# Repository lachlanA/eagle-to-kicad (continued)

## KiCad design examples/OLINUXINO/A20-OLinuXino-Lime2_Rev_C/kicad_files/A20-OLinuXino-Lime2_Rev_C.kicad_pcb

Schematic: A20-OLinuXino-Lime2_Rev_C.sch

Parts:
1.2V_CPU224, 1.2V_INT224, 1.5V224, 2.5V224, 3.0VA224, 3.3V224, 5VEXT224: TESTPADTESTPAD_40-ROUND; GOGO_TESTPAD_40-ROUND
5V_E224: Open; JUMPER_SJ_1_SMALLER
5V_E_SATA224: JUMPER_SJ_1_SMALLER
5V_SATA_PWR224: CON2DW02R; PENKO_DW02R
+5V224: TESTPADTESTPAD_40-ROUND; GOGO_TESTPAD_40-ROUND
BAT224: TESTPADTESTPAD_40-ROUND; GOGO_TESTPAD_40-ROUND
C1, C2, C3, C4, C5, C6, C7, C8, C9, C10, C11, C12, C13, C14, C16, C17, C18, C19, C20, C21, C22, C23, C24, C25, C26, C27, C28, C29, C30, C31, C32, C33, C34, C35, C36, C37, C38, C39, C40, C41, C42, C43, C44, C45, C46, C47, C48, C49, C50, C51, C52, C53, C54, C55, C56, C57, C58, C59, C60, C61, C62, C63, C64, C65, C66, C67, C68, C69, C70, C74, C75, C76, C92, C93, C94, C95, C96, C97, C98, C99, C100, C106, C107, C121, C126, C129, C130, C131, C132, C133, C144, C148, C164, C178, C184, C189, C194, C196: 220nF; RCL_C0402_TI
C15, C71, C77, C83, C86, C87, C118, C120, C122, C123, C124, C138, C143, C145, C147, C151, C165, C168, C177, C181, C190, C191, C192, C195, C198, C202, C203, C204, C205, C206, C207, C208, C210, C212, C213: 22uF/6.3V; RCL_C0603_DWS
C72, C73, C78, C79, C82, C84, C85, C88, C89, C90, C91, C101, C102, C103, C109, C112, C113, C114, C119, C135, C136, C137, C149, C152, C193: 100nF; RCL_C0402_TI
C80, C81: NA; RCL_C0402_TI
C104, C105: 27pF; RCL_C0603_DWS
C108, C125, C159, C171, C176, C180: 1uF; RCL_C0603_DWS
C110, C115: 10pF; RCL_C0402_TI
C111: 100n; RCL_C0402_TI
C116, C117: 33pF; RCL_C0603_DWS
C127, C128, C134, C146, C150, C155, C158, C160, C161, C162, C163, C166, C170, C172, C174, C179, C182, C183, C185, C186, C188: 10uF/6.3V; RCL_C0603_DWS
C139, C140, C141, C142, C167, C173, C187, C209: 1nF; RCL_C0402_TI
C153, C154, C156, C157: 10nF; RCL_C0402_TI
C169, C220, C221, C222, C223: NA(22uF/6.3V); RCL_C0603_DWS
C175: 22uF/6.3V/0603; RCL_C0603_DWS
C197, C199: 470nF; RCL_C0603_DWS
C200: 470uF/10V/105C; RCL_E2_5-6_3
C201, C211: 22pF; RCL_C0603_DWS
C214: 1nF/2kV/X7R/1206; RCL_C1206_5MILS_WS_ISO
C215, C216, C217, C218, C219: NA(47uF/6.3V/tant); RCL_CT3528_MIL
CHGLED224: LED/YELLOW/0603; DOUBLE-SIDE_LED-0603
D1, D2: 1N5819(S4SOD-123); GOGO_SOD-123
D3: SMBJ6.0A; OLIMEX_DISCRET_DO214AA
D4: NA(1N5822/SS34/SMA); GOGO_MLL-41
D5: 1N5822/SS34/SMA; SEMICON-SMD-IPC_MELF-MLL41
FET1, FET3, FET4: IRLML6402; PENKO_SOT23
FET2: BSS138; PENKO_SOT23
FUSE1: FSMD035; GOGO_1206
GND224: TESTPADTESTPAD_40-ROUND; GOGO_TESTPAD_40-ROUND
GND_PIN224: TESTPAD3; GOGO_TEST_PAD40_70_SQUARE
GPIO-1, GPIO-2, GPIO-3: GPH127SMT-02X20(PA-V16X-2X20-LF); CON-HARTING-ML_GPH127SMT-02X20(PA-V16X-2X20-LF)
GPIO-4: GPH127SMT-02X10(PA-V16X-2X10-LF); CON-HARTING-ML_GPH127SMT-02X10(PA-V16X-2X10-LF)
HDMI224: HDMI-SWM-19; OLIMEX_CONNECTORS_HDMI-SWM-19
IPSOUT224: TESTPADTESTPAD_40-ROUND; GOGO_TESTPAD_40-ROUND
L1, L2, L3: 0R/0805; RCL_L0805_5MIL_DWS
L4: 4.7uH/1.15A/DCR<0.1R/CD43; OLIMEX_DISCRET_CD42(43)
L5: CL470nH/0805/0.3R/250mA; RCL_L0805_5MIL_DWS
L6, L7, L8, L9, L10: FB0805/600R/2A; RCL_L0805_5MIL_DWS
L11, L12, L13, L14, L15, L16: 2.2uH/1.5A/DCR<0.1R/CD32; OLIMEX_DISCRET_CD32
LAN224: TM211Q01FM22_SH; OLIMEX_CONNECTORS_TM211Q01FM22_SH
LCD_CON224: GPH127SMT-02X20(PA-V16X-2X20-LF); CON-HARTING-ML_GPH127SMT-02X20(PA-V16X-2X20-LF)
LED1: LED/GREEN/0603; DOUBLE-SIDE_LED-0603
LIPO_BAT224: CON2DW02R; PENKO_DW02R
NAND_E224: Close; JUMPER_SJ_1_SMALLER_CLOSE_10MILS
PC3/PB8: JUMPER_SJ_2_SMALL_23_TIED
PWR224: SIDE_WTCM-TR(3X4); GOGO_SW_TAKT3X4
PWR_JACK224: YDJ-1136; GOGO_PWR_JACK_UNI_MILLING
PWR_LED224: LED/RED/0603; DOUBLE-SIDE_LED-0603
Q1: E4SB25.000F20E15(25MHz/20pF/20ppm/5x3.2mm); CRYSTAL_HCX-4S
Q3: 4SB24.000F20E15/5x3.2mm/20ppm/20pF; CRYSTAL_HCX-4S
Q4: 32768Hz/6pF; CRYSTAL_MC-306
R1, R2, R4, R5, R6, R45, R46: 2k/1%; RCL_R0402_TI
R3, R19, R28, R33, R34, R38: NA; RCL_R0402_TI
R7, R8, R14: 330R/1%; RCL_R0603_5MIL_DWS
R9, R10, R16, R17: 22R; RCL_R0402_TI
R11, R13: 0R_board_mounted; RCL_R0402_TI_0R
R12: NA(4.7k); RCL_R0402_TI
R15, R18, R22, R23, R29, R42, R44, R52, R54, R58, R62, R64, R68, R71, R78: 10k; RCL_R0402_TI
R20, R24, R36: 1k; RCL_R0402_TI
R21, R32, R37: 4.7k; RCL_R0402_TI
R25: NA(22R); RCL_R0402_TI
R26: 2.49k/1%; RCL_R0603_5MIL_DWS
R27, R30, R47, R55, R76: 47k; RCL_R0402_TI
R31: 470k; RCL_R0402_TI
R35: 10M; RCL_R0402_TI
R39, R40, R93, R94, R95, R96: NA(2.2k); RCL_R0402_TI
R41, R67, R87: 100k/1%; RCL_R0603_5MIL_DWS
R43, R69, R74: 200k/1%; RCL_R0603_5MIL_DWS
R48: NA(0R); RCL_R0603_5MIL_DWS
R49, R50: NA; RCL_R0603_5MIL_DWS
R51, R86, R91: 4.99k/1%; RCL_R0603_5MIL_DWS
R53, R63: 13k/1%; RCL_R0603_5MIL_DWS
R56, R57, R60, R61, R70, R75, R77, R79, R80, R81, R82, R88: 2.2k; RCL_R0402_TI
R59, R73: 6.8k/1%; RCL_R0603_5MIL_DWS
R65: 100R; RCL_R0603_5MIL_DWS
R66: 0.03R/1%; RCL_R1206_5MIL_WS
R72: 191R/1%; RCL_R0603_5MIL_DWS
R83: 0R(Board_Mounted); OLIMEX_DISCRET_0603_0R
R84: 1M; RCL_R0402_TI
R85: 8.25k/1%; RCL_R0603_5MIL_DWS
R89, R92: 1.1k/1%; RCL_R0603_5MIL_DWS
R90: 3.32k/1%; RCL_R0603_5MIL_DWS
RECOVERY224: SIDE_WTCM-TR(3X4); GOGO_SW_TAKT3X4
RESET224: SIDE_WTCM-TR(3X4); GOGO_SW_TAKT3X4
RM1, RM4: RA0805_(4X0402)_4B8_4.7k; OLIMEX_DISCRET_R_MATRIX_4_0402_25X625
RM2: RA0805_(4X0402)_4B8_22R; OLIMEX_DISCRET_R_MATRIX_4_0402_25X625
RM3: RA1206_(4X0603)_4B8_100K; OLIMEX_DISCRET_R_MATRIX_4
SATA224: SATA-PWA-07; OLIMEX_CONNECTORS_SATA-PWA-07
SD/MMC224: MICRO_SD/MMC_CP_NEWTFC-WPAPR-08; OLIMEX_CONNECTORS_TFC-WPAPR-08
T1: BC846B; SEMICON-SMD-IPC_SOT23
U1: A20; OLIMEX_IC_TFBGA441
U2, U3: K4B4G1646D-BCK0; OLIMEX_IC_FBGA96_SK
U4: H27UBG8T2BTR; OLIMEX_IC_TSOP48
U5: RTL8211CL-GR; OLIMEX_IC_LQFP48
U6: AT24C16BN-SH; GOGO_SO-08MN
U7, U8, U9: NA(RCLAMP0524P); OLIMEX_IC_SLP2510P8
U10, U11, U12: SY6280; OLIMEX_IC_SOT23-5
U13: AXP209(QFN48); OLIMEX_IC_QFN48
U14: MCP120T475I-TT; GOGO_SOT23
U15, U17: SY8008C(AA)C; OLIMEX_IC_SOT23-5
U16: SY7208(SOT23-6); OLIMEX_IC_SOT23-6
U18, U19, U20, U21: FIDUCIAL; SPARKFUNEAGLE-6-6-07_FIDUCIAL-1X3
UART0: HN1X3; PENKO_HN1X3
USB_HOST1, USB_HOST2: USB_A_VERTICAL; OLIMEX_CONNECTORS_USB_A_VERTICAL_PTH
USB_OTG224: USB-OTG; OLIMEX_CONNECTORS_USB_MINI_9PIN
VR1: AP1231-2.5V(SOT23-5); OLIMEX_DISCRET_SOT-23-5

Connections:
+5V: GPIO-1.1, GPIO-2.1, GPIO-3.1, LCD_CON224.1
/5VEXT: 5VEXT224.1, 5V_E224.1, C158.2, C200.+, D3.C, D4.A, FET3.3 (D), PWR_JACK224.+, R78.1, R82.1, U13.32 (ACIN), U13.33 (ACIN), U14.2 (VCC)
/+5V: 5V_E224.2, 5V_E_SATA224.1, +5V224.1, C137.1, C146.1, C150.1, D4.K (C), FET1.2 (S), FET3.2 (S), FET4.2 (S), FUSE1.1, R45.2, R46.2, R68.1, R76.2, U10.5 (IN), U11.5 (IN), U12.5 (IN)
/+5V_OTG_PWR: C136.1, C163.2, L6.1, R67.1, U13.31 (VBUS), USB_OTG224.VBUS
/+24V: BAT224.1, C159.2, C161.1, C207.2, LIPO_BAT224.1, R66.2, U13.38 (BAT), U13.39 (BAT), U13.42 (BATSENSE)
/AVDD1: C71.2, C72.2, C73.2, L1.2, U5.6 (AVDD33), U5.41 (AVDD33)
/AVDD/DVDD(1.05V): C86.2, C87.2, C88.2, C89.2, C90.2, C91.2, C101.2, U5.3 (FB10), U5.10 (AVDD10), U5.28 (DVDD10), U5.36 (DVDD10), U5.40 (AVDD10)
/BA0: U1.K3 (SBA0), U2.M2 (BA0), U3.M2 (BA0)
/BA1: U1.L4 (SBA1), U2.N8 (BA1), U3.N8 (BA1)
/BA2: U1.K4 (SBA2), U2.M3 (BA2), U3.M3 (BA2)
/CASN: U1.U3 (SCAS), U2.K3 (#CAS), U3.K3 (#CAS)
/CKE: U1.N3 (SCKE0), U2.K9 (CKE), U3.K9 (CKE)
/CLK: R9.1, U2.J7 (CK), U3.J7 (CK)
/CLK125: R25.1, U1.D13 (ECOL/CAN_TX/UART1_DCD/PA16)
/CLKN: R10.1, U2.K7 (#CK), U3.K7 (#CK)
/CPU-REF: C2.2, C13.2, C80.2, R2.1, R3.2, R5.2, U1.AA8 (SVREF3), U1.H3 (SVREF0), U1.H4 (SVREF1), U1.Y5 (SVREF2)
/DDR3_ODT: R13.1, U2.K1 (ODT), U3.K1 (ODT)
/DDR3_RST: R6.1, R11.1, U2.T2 (#RESET), U3.T2 (#RESET)
/DDR_VREF: C1.2, C14.2, R1.1, R3.1, R4.2, U2.H1 (VREFDQ), U2.M8 (VREFCA), U3.H1 (VREFDQ), U3.M8 (VREFCA)
/DQ0: U1.AB4 (SDQ0), U2.E3 (DQL0)
/DQ1: U1.AC7 (SDQ1), U2.F7 (DQL1)
/DQ2: U1.AC4 (SDQ2), U2.F2 (DQL2)
/DQ3: U1.AB8 (SDQ3), U2.F8 (DQL3)
/DQ4: U1.AC8 (SDQ4), U2.H3 (DQL4)
/DQ5: U1.AB5 (SDQ5), U2.H8 (DQL5)
/DQ6: U1.AB7 (SDQ6), U2.G2 (DQL6)
/DQ7: U1.AC3 (SDQ7), U2.H7 (DQL7)
/DQ8: U1.AB2 (SDQ8), U2.D7 (DQU0)
/DQ9: U1.Y1 (SDQ9), U2.C3 (DQU1)
/DQ10: U1.AC2 (SDQ10), U2.C8 (DQU2)
/DQ11: U1.Y2 (SDQ11), U2.C2 (DQU3)
/DQ12: U1.AA1 (SDQ12), U2.A7 (DQU4)
/DQ13: U1.AB3 (SDQ13), U2.A2 (DQU5)
/DQ14: U1.W2 (SDQ14), U2.B8 (DQU6)
/DQ15: U1.AC1 (SDQ15), U2.A3 (DQU7)
/DQ16: U1.N1 (SDQ16), U3.E3 (DQL0)
/DQ17: U1.T2 (SDQ17), U3.F7 (DQL1)
/DQ18: U1.N2 (SDQ18), U3.F2 (DQL2)
/DQ19: U1.U1 (SDQ19), U3.F8 (DQL3)
/DQ20: U1.U2 (SDQ20), U3.H3 (DQL4)
/DQ21: U1.P1 (SDQ21), U3.H8 (DQL5)
/DQ22: U1.T1 (SDQ22), U3.G2 (DQL6)
/DQ23: U1.M2 (SDQ23), U3.H7 (DQL7)
/DQ24: U1.L1 (SDQ24), U3.D7 (DQU0)
/DQ25: U1.H1 (SDQ25), U3.C3 (DQU1)
/DQ26: U1.L2 (SDQ26), U3.C8 (DQU2)
/DQ27: U1.H2 (SDQ27), U3.C2 (DQU3)
/DQ28: U1.J1 (SDQ28), U3.A7 (DQU4)
/DQ29: U1.M1 (SDQ29), U3.A2 (DQU5)
/DQ30: U1.G2 (SDQ30), U3.B8 (DQU6)
/DQ31: U1.K2 (SDQ31), U3.A3 (DQU7)
/DVDD33: C77.2, C78.2, C79.2, C82.2, L2.2, R18.1, R31.1, U5.15 (DVDD33), U5.21 (DVDD33), U5.37 (DVDD33)
/EPHY-RST#: R38.1, U1.C13 (ETXERR/CAN_RX/UART1_RING/PA17)
/EXTEN: U13.20 (EXTEN), U16.4 (EN), U17.1 (EN)
/FMINL: U1.Y20 (FMINL)
/FMINR: U1.Y21 (FMINR)
/GMDC: U1.E10 (EMDC/UART1_RX/PA11), U5.30 (MDC)
/GMDIO: R24.1, U1.D11 (EMDIO/UART6_TX/UART1_RTS/PA12), U5.31 (MDIO)
/GPIO1: R67.2, R69.1, U13.18 (GPIO1)
/GRXCK: R17.2, U1.D9 (ERXCK/SPI3_MISO/PA8)
/GRXD0: RM2.4.2 (2), U1.E6 (ERXD0/SPI1_MISO/PA3)
/GRXD1: RM2.3.2 (2), U1.D6 (ERXD1/SPI1_MOSI/PA2)
/GRXD2: RM2.2.2 (2), U1.E5 (ERXD2/SPI1_CLK/PA1)
/GRXD3: RM2.1.2 (2), U1.D5 (ERXD3/SPI1_CS0/PA0)
/GTXCK: U1.E12 (ECRS/UART7_RX/UART1_DSR/PA15), U5.22 (TXC)
/GTXCTL: U1.E11 (ETXEN/UART6_RX/UART1_CTS/PA13), U5.27 (TXCTL/TXEN)
/GTXD0: U1.E8 (ETXD0/SPI3_MOSI/PA7), U5.23 (TXD[0])
/GTXD1: U1.D8 (ETXD1/SPI3_CLK/PA6), U5.24 (TXD[1])
/GTXD2: U1.E7 (ETXD2/SPI3_CS0/PA5), U5.25 (TXD[2])
/GTXD3: U1.D7 (ETXD3/SPI1_CS1/PA4), U5.26 (TXD[3])
/HCEC: HDMI224.13, U1.P23 (CEC_HDMI), U9.1 (IN1), U9.10 (OUT1)
/HDMI_5V_SOURCE: FUSE1.2, HDMI224.18
/HHPD: HDMI224.19, R47.1, U1.P22 (HPD_HDMI), U9.5 (IN4), U9.6 (OUT4)
/HPCOM: U1.AA19 (HPCOM), U1.AA20 (HPCOMFB)
/HPOUTL: U1.Y19 (HPOUTL)
/HPOUTR: U1.W19 (HPOUTR)
/HSCL: HDMI224.15, R45.1, U1.R23 (SCL_HDMI), U9.2 (IN2), U9.9 (OUT2)
/HSDA: HDMI224.16, R46.1, U1.R22 (SDA_HDMI), U9.4 (IN3), U9.7 (OUT3)
/HTX0N: HDMI224.9, U1.V22 (TX0N_HDMI), U8.2 (IN2), U8.9 (OUT2)
/HTX0P: HDMI224.7, U1.V23 (TX0P_HDMI), U8.1 (IN1), U8.10 (OUT1)
/HTX1N: HDMI224.6, U1.U22 (TX1N_HDMI), U7.5 (IN4), U7.6 (OUT4)
/HTX1P: HDMI224.4, U1.U23 (TX1P_HDMI), U7.4 (IN3), U7.7 (OUT3)
/HTX2N: HDMI224.3, U1.T22 (TX2N_HDMI), U7.2 (IN2), U7.9 (OUT2)
/HTX2P: HDMI224.1, U1.T23 (TX2P_HDMI), U7.1 (IN1), U7.10 (OUT1)
/HTXCN: HDMI224.12, U1.W22 (TXCN_HDMI), U8.5 (IN4), U8.6 (OUT4)
/HTXCP: HDMI224.10, U1.W23 (TXCP_HDMI), U8.4 (IN3), U8.7 (OUT3)
/IPSOUT: C155.2, C162.1, C170.1, C174.1, C182.2, C186.1, C202.1, C208.2, C210.1, IPSOUT224.1, L15.1, R70.1, U13.7 (VIN2), U13.13 (LDO24IN), U13.14 (VIN3), U13.21 (APS), U13.34 (IPSOUT), U13.35 (IPSOUT), U13.40 (LDO3IN), U13.44 (VIN1), U15.4 (IN), U16.5 (IN), U17.4 (IN)
/LAN_SH: C214.2, LAN224.SH1, LAN224.SH2
/LCD_CLK: U1.Y9 (LCD0_CLK/SMC_VCCEN/PD24)
/LCD_D0: U1.AB15 (LCD0_D0/LVDS0_VP0/PD0)
/LCD_D1: U1.AC15 (LCD0_D1/LVDS0_VN0/PD1)
/LCD_D2: U1.AB14 (LCD0_D2/LVDS0_VP1/PD2)
/LCD_D3: U1.AC14 (LCD0_D3/LVDS0_VN1/PD3)
/LCD_D4: U1.AB13 (LCD0_D4/LVDS0_VP2/PD4)
/LCD_D5: U1.AC13 (LCD0_D5/LVDS0_VN2/PD5)
/LCD_D6: U1.AB12 (LCD0_D6/LVDS0_VPC/PD6)
/LCD_D7: U1.AC12 (LCD0_D7/LVDS0_VNC/PD7)
/LCD_D8: U1.AB11 (LCD0_D8/LVDS0_VP3/PD8)
/LCD_D9: U1.AC11 (LCD0_D9/LVDS0_VN3/PD9)
/LCD_D10: U1.Y15 (LCD0_D10/LVDS1_VP0/PD10)
/LCD_D11: U1.AA15 (LCD0_D11/LVDS1_VN0/PD11)
/LCD_D12: U1.Y14 (LCD0_D12/LVDS1_VP1/PD12)
/LCD_D13: U1.AA14 (LCD0_D13/LVDS1_VN1/PD13)
/LCD_D14: U1.Y13 (LCD0_D14/LVDS1_VP2/PD14)
/LCD_D15: U1.AA13 (LCD0_D15/LVDS1_VN2/PD15)
/LCD_D16: U1.Y12 (LCD0_D16/LVDS1_VPC/PD16)
/LCD_D17: U1.AA12 (LCD0_D17/LVDS1_VNC/PD17)
/LCD_D18: U1.Y11 (LCD0_D18/LVDS1_VP3/PD18)
/LCD_D19: U1.AA11 (LCD0_D19/LVDS1_VN3/PD19)
/LCD_D20: U1.Y10 (LCD0_D20/CSI1_MCLK/PD20)
/LCD_D21: U1.AA10 (LCD0_D21/SMC_VPPEN/PD21)
/LCD_D22: U1.AB10 (LCD0_D22/SMC_VPPPP/PD22)
/LCD_D23: U1.AC10 (LCD0_D23/SMC_DET/PD23)
/LCD_DE: U1.AA9 (LCD0_DE/SMC_RST/PD25)
/LCD_HSYNC: U1.AB9 (LCD0_HSYNC/SMC_SLK/PD26)
/LCD_PWR: U1.C4 (LCD1_D8/ATAD4/KP_IN0/MS_D0/EINT8/CSI1_D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)
/LCD_VSYNC: U1.AC9 (LCD0_VSYNC/SMC_SDA/PD27)
/LDO3_2.8V: C106.2, C185.1, U1.F19 (VCC_CSI0), U13.41 (LDO3)
/LDO4_2.8V: C107.2, C188.1, U1.E18 (VCC_CSI1), U13.11 (LDO4)
/LINEINL: U1.AB20 (LINEINL)
/LINEINR: U1.AB21 (LINEINR)
/LRADC0: C209.1, R87.2, U1.AB23 (LRADC0)
/LRADC1: U1.AB22 (LRADC1)
/MDI[0]+: LAN224.1, U5.1 (MDI[0]+)
/MDI[0]-: LAN224.2, U5.2 (MDI[0]-)
/MDI[1]+: LAN224.3, U5.4 (MDI[1]+)
/MDI[1]-: LAN224.4, U5.5 (MDI[1]-)
/MDI[2]+: LAN224.7, U5.8 (MDI[2]+)
/MDI[2]-: LAN224.8, U5.9 (MDI[2]-)
/MDI[3]+: LAN224.9, U5.11 (MDI[3]+)
/MDI[3]-: LAN224.10, U5.12 (MDI[3]-)
/MIC1OUTN: U1.AC23 (MIC1OUTN)
/MIC1OUTP: U1.AC22 (MIC1OUTP)
/MICIN1: U1.AC20 (MICIN1)
/MICIN2: U1.AC21 (MICIN2)
/N$1: C133.2, C134.2, U1.AC19 (HPVCC)
/N$2: R14.2, U1.AA7 (SZQ)
/N$3: R7.2, U2.L8 (ZQ)
/N$4: CHGLED224.A, R70.2
/N$5: PC3/PB8.2, R71.2
/N$7: UART0.2
/N$8: L14.1, U15.3 (LX)
/N$9: C171.2, U13.19 (GPIO0/LDO)
/N$10: R27.2
/N$11: CHGLED224.C, U13.36 (CHGLED)
/N$12: R80.1, U13.27 (LDO1SET)
/N$13: C151.2, C217.+, C218.+, C221.2, C222.2, C223.2, L10.1, U12.1 (OUT)
/N$14: C110.2, Q4.1, R35.1, U1.F1 (CLK32K_IN)
/N$15: R8.2, U3.L8 (ZQ)
/N$16: U5.48 (REG_OUT)
/N$17: C175.1, R71.1, R73.2, T1.1 (B)
/N$18: FET1.1 (G), R68.2, T1.3 (C)
/N$19: C201.2, R86.2, R90.1, U15.5 (FB)
/N$20: R26.2, U5.46 (RSET)
/N$21: FET3.1 (G), R76.1
/N$22: C104.2, Q1.2, U5.42 (CKXTAL1)
/N$23: C205.1, C206.1, D5.1 (C), FET4.3 (D), R85.2
/N$24: 5V_E_SATA224.2, 5V_SATA_PWR224.1, C168.2, C169.2, FET1.3 (D)
/N$25: C105.2, Q1.1, U5.43 (CKXTAL2)
/N$26: C111.2, R31.2, R34.2, R38.2, U5.29 (PHYRSTB)
/N$27: C102.2, LAN224.5
/N$28: C103.2, LAN224.6
/N$29: R33.1, R37.1, U5.38 (RXDLY/LED_10/LED2)
/N$30: LAN224.12, R36.2
/N$31: LAN224.11, R32.2, U5.35 (PHY_AD1/LED_1000/LED1)
/N$33: FET4.1 (G), R78.2, R84.2, U14.1 (RESET)
/N$34: R18.2, R19.2, U5.39 (ENSWREG)
/N$35: LAN224.13, R20.2
/N$36: C81.1, R17.1, U5.19 (RXC)
/N$37: R15.1, R16.1, U5.13 (RXCTL/RXDV)
/N$38: R75.1
/N$42: C197.2, U1.AA16 (VRP_TVIN)
/N$43: RM2.4.1 (1), U5.14 (RXD[0])
/N$44: R12.1, RM1.3.1 (1), RM2.3.1 (1), U5.16 (RXD[1]/TXDLY)
/N$46: RM1.2.1 (1), RM2.2.1 (1), U5.17 (RXD[2]/AN0)
/N$48: RM1.1.1 (1), RM2.1.1 (1), U5.18 (RXD[3]/AN1)
/N$50: LAN224.14, R21.1, U5.34 (PHY_AD0/LED_DUPLEX/LED0)
/N$52: R25.2, U5.32 (CLK125)
/N$58: R44.1, SD/MMC224.10 (PACK1), SD/MMC224.11 (PACK2), SD/MMC224.12 (PACK3), SD/MMC224.13 (PACK4)
/N$64: L16.1, U17.3 (LX)
/N$66: C211.2, R91.2, R92.1, U17.5 (FB)
/N$99: R53.2, U10.3 (ISET)
/N$100: C138.2, C219.+, L6.2, R51.2, U10.1 (OUT)
/N$101: R63.2, U12.3 (ISET)
/N$106: C153.2, SATA224.2 (A+)
/N$111: C152.1, L10.2, USB_HOST2.1
/N$112: C154.2, SATA224.3 (A-)
/N$113: C156.2, SATA224.5 (B-)
/N$114: C157.2, SATA224.6 (B+)
/N$116: C115.2, Q4.4 (2), R35.2, U1.F2 (CLK32K_OUT)
/N$119: R72.2, U1.V21 (REXT_SATA)
/N$120: R74.2, U13.23 (BIAS)
/N$122: C128.2, C129.2, U1.W21 (VRP)
/N$123: D5.2 (A), L15.2, U16.1 (LX)
/N$124: C112.2, R28.2, R29.2, U4.19 (#WP)
/N$125: R65.2, U13.37 (TS)
/N$126: R85.1, R89.1, U16.3 (FB)
/N$127: L11.1, U13.45 (LX1)
/N$128: C159.1, C160.1, L11.2, R66.1, U13.43 (CHSENSE)
/N$129: PWR_LED224.A, R82.2
/N$130: L12.1, U13.8 (LX2)
/N$131: L13.1, U13.15 (LX3)
/N$132: C180.2, U13.24 (VREF)
/N$133: C125.2, U1.W20 (VRA1)
/N$137: R59.2, U11.3 (ISET)
/N$139: C187.2, R75.2, U13.47 (PWRON)
/N$140: R77.2, U13.4 (N_OE)
/N$176: C126.2, C127.2, R43.1, U1.V20 (VRA2)
/N$190: R48.1, U1.T10 (JTAG_SEL)
/N$193: L9.2, USB_HOST1.P$3 (5), USB_HOST1.P$4 (6), USB_HOST2.P$3 (5), USB_HOST2.P$4 (6)
/N$194: C149.1, L8.2, USB_HOST1.1
/N$195: C147.2, C215.+, C216.+, C220.2, L8.1, U11.1 (OUT)
/N$223: C199.2, U1.Y16 (VRN_TVIN)
/N$229: R49.1
/N$230: R50.1
/N$231: LED1.A, R88.2
/N$232: NAND_E224.1, R23.2, U4.9 (#CE)
/N$266: L7.2, USB_OTG224.GND1, USB_OTG224.GND2, USB_OTG224.GND3, USB_OTG224.GND4
/NALE: U1.M22 (NALE/SPI0_MISO/PC1), U4.17 (ALE)
/NCE0: NAND_E224.2, U1.K23 (NCE0/PC4)
/NCLE: U1.L23 (NCLE/SPI0_CLK/PC2), U4.16 (CLE)
/NDQ0: U1.H23 (NDQ0/SDC2_D0/PC8), U4.29 (I/O0)
/NDQ1: U1.H22 (NDQ1/SDC2_D1/PC9), U4.30 (I/O1)
/NDQ2: U1.G23 (NDQ2/SDC2_D2/PC10), U4.31 (I/O2)
/NDQ3: U1.G22 (NDQ3/SDC2_D3/PC11), U4.32 (I/O3)
/NDQ4: U1.H21 (NDQ4/PC12), U4.41 (I/O4)
/NDQ5: U1.H20 (NDQ5/PC13), U4.42 (I/O5)
/NDQ6: U1.G21 (NDQ6/PC14), U4.43 (I/O6)
/NDQ7: U1.G20 (NDQ7/PC15), U4.44 (I/O7)
/NMI_N: R27.1, U1.F5 (NMI#), U13.48 (IRQ/WAKEUP)
/NRB0: R22.2, U1.J23 (NRB0/SDC2_CMD/PC6), U4.7 (R/#B)
/NRE: U1.K22 (NRE#/PC5), U4.8 (#RE)
/NWE: U1.M23 (NWE#/SPI0_MOSI/PC0), U4.18 (#WE)
/ODT0: R13.2, U1.AA5 (ODT0)
/PA9: U1.E9 (ERXERR/SPI3_CS1/PA9)
/PA14: U1.D12 (ETXCK/UART7_TX/UART1_DTR/PA14)
/PB2/PWM0: U1.A14 (PWM0/PB2)
/PB3: R49.2, U1.B14 (IR0_TX/SPDIF_MCLK/STANBYWFI/PB3)
/PB4: R50.2, U1.A13 (IR0_RX/PB4)
/PB5: U1.B13 (I2S_MCLK/AC97_MCLK/PB5)
/PB6: U1.A12 (I2S_BCLK/AC97_BCLK/PB6)
/PB7: U1.B12 (I2S_LRCK/AC97_SYNC/PB7)
/PB8/SATA-PWR-EN: PC3/PB8.1, U1.A11 (I2S_DO0/AC97_DO/PB8)
/PB9: U1.C12 (I2S_DO1/PB9)
/PB10: U1.C11 (I2S_DO2/PB10)
/PB11: U1.C10 (I2S_DO3/PB11)
/PB12: U1.C9 (I2S_DI/AC97_DI/SPDIF_DI/PB12)
/PB13: U1.B11 (SPI2_CS1/SPDIF_DO/PB13)
/PB14: RM4.1.1 (1), U1.A10 (JTAG_MS0/SPI2_CS0/PB14)
/PB15: RM4.2.1 (1), U1.B10 (JTAG_CK0/SPI2_CLK/PB15)
/PB16: U1.A9 (JTAG_DO0/SPI2_MOSI/PB16)
/PB17: RM4.4.1 (1), U1.B9 (JTAG_DI0/SPI2_MISO/PB17)
/PB18: R39.2, R61.1, U1.A8 (TWI1_SCK/PB18), U6.6 (SCL)
/PB19: R40.1, R60.1, U1.B8 (TWI1_SDA/PB19), U6.5 (SDA)
/PB20: R57.1, U1.C8 (TWI2_SCK/PB20)
/PB21: R56.1, U1.C7 (TWI2_SDA/PB21)
/PC3/SATA-PWR-EN: PC3/PB8.3, U1.L22 (NCE1/PC3)
/PC7: U1.J22 (NRB1/SDC2_CLK/PC7)
/PC16/NWP: R28.1, U1.M21 (NWP/PC16)
/PC17/USB0-DRV: R52.2, U1.F23 (NCE2/PC17), U10.4 (EN), U13.6 (N_VBUSEN)
/PC18: U1.F22 (NCE3/PC18)
/PC19: U1.L21 (NCE4/SPI2_CS0/PC19)
/PC20: U1.K21 (NCE5/SPI2_CLK/PC20)
/PC21: U1.J21 (NCE6/SPI2_MOSI/PC21)
/PC22: U1.J20 (NCE7/SPI2_MISO/PC22)
/PC23: U1.G19 (SPI0_CS0/PC23)
/PC24: U1.F21 (NDQS/PC24)
/PE0: U1.E23 (TS0_CLK/CSI0_PCLK/PE0)
/PE1: U1.E22 (TS0_ERR/CSI0_MCLK/PE1)
/PE2: U1.D23 (TS0_SYNC/CSI0_HSYNC/PE2)
/PE3: U1.D22 (TS0_DVLD/CSI0_VSYNC/PE3)
/PE4: U1.C23 (TS0_D0/CSI0_D0/PE4)
/PE5: U1.C22 (TS0_D1/CSI0_D1/PE5)
/PE6: U1.B23 (TS0_D2/CSI0_D2/PE6)
/PE7: U1.B22 (TS0_D3/CSI0_D3/PE7)
/PE8: U1.A23 (TS0_D4/CSI0_D4/PE8)
/PE9: U1.A22 (TS0_D5/CSI0_D5/PE9)
/PE10: U1.B21 (TS0_D6/CSI0_D6/PE10)
/PE11: U1.A21 (TS0_D7/CSI0_D7/PE11)
/PG0: U1.F20 (TS1_CLK/CSI1_PCLK/SDC1_CMD/PG0)
/PG1: U1.E21 (TS1_ERR/CSI1_MLCK/SDC1_CLK/PG1)
/PG2: U1.E20 (TS1_SYNC/CSI1_HSYNC/SDC1_D0/PG2)
/PG3: U1.D21 (TS1_DVLD/CSI1_VSYNC/SDC1_D1/PG3)
/PG4: U1.D20 (TS1_D0/CSI1_D0/SDC1_D2/CSI0_D8/PG4)
/PG5: U1.C21 (TS1_D1/CSI1_D1/SDC1_D3/CSI0_D9/PG5)
/PG6: U1.E19 (TS1_D2/CSI1_D2/UART3_TX/CSI0_D10/PG6)
/PG7: U1.C20 (TS1_D3/CSI1_D3/UART3_RX/CSI0_D11/PG7)
/PG8: U1.D19 (TS1_D4/CSI1_D4/UART3_RTS/CSI0_D12/PG8)
/PG9: U1.C19 (TS1_D5/CSI1_D5/UART3_CTS/CSI0_D13/PG9)
/PG10: U1.D18 (TS1_D6/CSI1_D6/UART4_TX/CSI0_D14/PG10)
/PG11: U1.C18 (TS1_D7/CSI1_D7/UART4_RX/CSI0_D15/PG11)
/PH0: U1.A6 (LCD1_D0/ATAA0/UART3_TX/EINT0/CSI1_D0/PH0)
/PH2/LED: R88.1, U1.C6 (LCD1_D2/ATAA2/UART3_RTS/EINT2/CSI1_D2/P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)
/PH7: U1.B4 (LCD1_D7/ATAD3/UART5_RX/MS_CLK/EINT7/CSI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)
/PH9: U1.D4 (LCD1_D9/ATAD5/KP_IN1/MS_D1/EINT9/CSI1_D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)
/PH10: U1.A3 (LCD1_D10/ATAD6/KP_IN2/MS_D2/EINT10/CSI1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)
/PH11: U1.B3 (LCD1_D11/ATAD7/KP_IN3/MS_D3/EINT11/CSI1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)
/PH12: U1.C3 (LCD1_D12/ATAD8/PS2_SCK1/EINT12/CSI1_D12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)
/PH13: U1.A2 (LCD1_D13/ATAD9/PS2_SDA1/SMC_RST/EINT13/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)
/PH14: U1.B2 (LCD1_D14/ATAD10/KP_IN4/SMC_VPPEN/EINT14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)
/PH15: U1.A1 (LCD1_D15/ATAD11/KP_IN5/SMC_VPPPP/EINT15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)
/PH16: U1.B1 (LCD1_D16/ATAD12/KP_IN6/SMC_DET/EINT16/C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)
/PH17: U1.C1 (LCD1_D17/ATAD13/KP_IN7/SMC_VCCEN/EINT17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)
/PH18: U1.C2 (LCD1_D18/ATAD14/KP_OUT0/SMC_SLK/EINT18/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)
/PH19: U1.D1 (LCD1_D19/ATAD15/KP_OUT1/SMC_SDA/EINT19/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)
/PH20: U1.D2 (LCD1_D20/ATAOE/CAN_TX/EINT20/CSI1_D20/P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)
/PH21: U1.D3 (LCD1_D21/ATADREQ/CAN_RX/EINT21/CSI1_D21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)
/PH22: U1.E1 (LCD1_D22/ATADACK/KP_OUT2/SDC1_CMD/CSI1_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)
/PH23: U1.E2 (LCD1_D23/ATACS0/KP_OUT3/SDC1_CLK/CSI1_D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)
/PH24: U1.E3 (LCD1_CLK/ATACS1/KP_OUT4/SDC1_D0/CSI1_PC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)
/PH25: U1.E4 (LCD1_DE/ATAIORDY/KP_OUT5/SDC1_D1/CSI1_F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)
/PH26: U1.F3 (LCD1_HSYNC/ATAIOR/KP_OUT6/SDC1_D2/CSI1_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)
/PH27: U1.F4 (LCD1_VSYNC/ATAIOW/KP_OUT7/SDC1_D3/CSI1_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)
/PI0: R93.1, U1.A20 (GPS_CLK/PI0)
/PI1: R94.1, U1.B20 (GPS_SIGN/PI1)
/PI2: R95.1, U1.A19 (GPS_MAG/PI2)
/PI3: R96.1, U1.B19 (PWM1/PI3)
/PI4: U1.A18 (SDC3_CMD/PI4)
/PI5: U1.B18 (SDC3_CLK/PI5)
/PI6: U1.A17 (SDC3_D0/PI6)
/PI7: U1.B17 (SDC3_D1/PI7)
/PI8: U1.A16 (SDC3_D2/PI8)
/PI9: U1.B16 (SDC3_D3/PI9)
/PI10: U1.C17 (SPI0_CS0/UART5_TX/EINT22/PI10)
/PI11: U1.D17 (SPI0_CLK/UART5_RX/EINT23/PI11)
/PI12: U1.C16 (SPI0_MOSI/UART6_TX/EINT24/PI12)
/PI13: U1.D16 (SPI0_MISO/UART6_RX/EINT25/PI13)
/PI14: U1.C15 (PS2_SCK1/TCLKIN0/EINT26/SPI0_CS1/PI14)
/PI15: U1.D15 (PS2_SDA1/TCLKIN1/EINT27/SPI1_CS1/PI15)
/PI16: U1.E17 (EINT28/SPI1_CS0/UART2_RTS/PI16)
/PI17: U1.E16 (EINT29/SPI1_CLK/UART2_CTS/PI17)
/PI18: U1.E15 (EINT30/SPI1_MOSI/UART2_TX/PI18)
/PI19: U1.D14 (EINT31/SPI1_MISO/UART2_RX/PI19)
/PI20: U1.E14 (HSCL/UART7_TX/PS2_SCK0/PI20)
/PI21: U1.E13 (HSDA/UART7_RX/PS2_SDA0/PI21)
/RASN: U1.T4 (SRAS), U2.J3 (#RAS), U3.J3 (#RAS)
/RESET_N: C108.2, C109.2, R30.1, R34.1, U1.C14 (RESET#), U13.25 (PWROK)
/RXDV: R16.2, U1.D10 (ERXDV/UART1_TX/PA10)
/SA0: U1.W4 (SA0), U2.N3 (A0), U3.N3 (A0)
/SA1: U1.R4 (SA1), U2.P7 (A1), U3.P7 (A1)
/SA2: U1.U4 (SA2), U2.P3 (A2), U3.P3 (A2)
/SA3: U1.M4 (SA3), U2.N2 (A3), U3.N2 (A3)
/SA4: U1.Y4 (SA4), U2.P8 (A4), U3.P8 (A4)
/SA5: U1.N4 (SA5), U2.P2 (A5), U3.P2 (A5)
/SA6: U1.V4 (SA6), U2.R8 (A6), U3.R8 (A6)
/SA7: U1.M3 (SA7), U2.R2 (A7), U3.R2 (A7)
/SA8: U1.AA3 (SA8), U2.T8 (A8), U3.T8 (A8)
/SA9: U1.P4 (SA9), U2.R3 (A9), U3.R3 (A9)
/SA10: U1.L3 (SA10), U2.L7 (A10/AP), U3.L7 (A10/AP)
/SA11: U1.W3 (SA11), U2.R7 (A11), U3.R7 (A11)
/SA12: U1.P3 (SA12), U2.N7 (A12/#BC), U3.N7 (A12/#BC)
/SA13: U1.Y3 (SA13), U2.T3 (A13), U3.T3 (A13)
/SA14: U1.R3 (SA14), U2.T7 (NC/A14), U3.T7 (NC/A14)
/SA15: U1.AA4 (SCS1), U2.M7 (NC), U3.M7 (NC)
/SATA-RXM: C156.1, U1.U20 (RXM_SATA)
/SATA-RXP: C157.1, U1.U21 (RXP_SATA)
/SATA-TXM: C154.1, U1.T21 (TXM_SATA)
/SATA-TXP: C153.1, U1.T20 (TXP_SATA)
/SCK: R9.2, U1.V1 (SCK)
/SCK#: R10.2, U1.V2 (SCK#)
/SCS0: U1.V3 (SCS0), U2.L2 (#CS), U3.L2 (#CS)
/SD0-CLK: SD/MMC224.5 (CLK/SCLK), U1.L20 (SDC0_CLK/UART0_TX/PF2)
/SD0-CMD: R42.1, SD/MMC224.3 (CMD/DI), U1.L19 (SDC0_CMD/JTAG_DO1/PF3)
/SD0-D0: RM3.2.2 (2), SD/MMC224.7 (DAT0/DO), U1.M19 (SDC0_D0/JTAG_DI1/PF1)
/SD0-D1: RM3.3.2 (2), SD/MMC224.8 (DAT1/RES), U1.M20 (SDC0_D1/JTAG_MS1/PF0)
/SD0-D2: RM3.1.2 (2), SD/MMC224.1 (DAT2/RES), U1.K19 (SDC0_D2/JTAG_CK1/PF5)
/SD0-D3: R41.1, SD/MMC224.2 (CD/DAT3/CS), U1.K20 (SDC0_D3/UART0_RX/PF4)
/SD0-DET#: RM3.4.2 (2), SD/MMC224.9 (CP_E), U1.B6 (LCD1_D1/ATAA1/UART3_RX/EINT1/CSI1_D1/PH1)
/SDQM0: U1.AC6 (SDQM0), U2.E7 (DML)
/SDQM1: U1.W1 (SDQM1), U2.D3 (DMU)
/SDQM2: U1.R2 (SDQM2), U3.E7 (DML)
/SDQM3: U1.G1 (SDQM3), U3.D3 (DMU)
/SDQS0: U1.AB6 (SDQS0), U2.F3 (DQSL)
/SDQS0_N: U1.AC5 (SDQS0#), U2.G3 (#DQSL)
/SDQS1: U1.AB1 (SDQS1), U2.C7 (DQSU)
/SDQS1_N: U1.AA2 (SDQS1#), U2.B7 (#DQSU)
/SDQS2: U1.R1 (SDQS2), U3.F3 (DQSL)
/SDQS2_N: U1.P2 (SDQS2#), U3.G3 (#DQSL)
/SDQS3: U1.K1 (SDQS3), U3.C7 (DQSU)
/SDQS3_N: U1.J2 (SDQS3#), U3.B7 (#DQSU)
/SD_VCC: C122.2, C124.2, L5.2, SD/MMC224.4 (VDD)
/SRST: R11.2, U1.AA6 (SRST)
/TPX1: C139.2, U1.Y22 (XP_TP)
/TPX2: C140.2, U1.AA22 (XN_TP)
/TPY1: C141.2, U1.Y23 (YP_TP)
/TPY2: C142.2, U1.AA23 (YN_TP)
/TVIN0: U1.AC18 (TVIN0)
/TVIN1: U1.AB18 (TVIN1)
/TVIN2: U1.AA17 (TVIN2)
/TVIN3: U1.Y17 (TVIN3)
/TVOUT3: U1.AB17 (TVOUT3)
/TWI0-SCK: R79.1, U1.A15 (TWI0_SCK/PB0), U13.2 (SCK)
/TWI0-SDA: R81.1, U1.B15 (TWI0_SDA/PB1), U13.1 (SDA)
/UART0-RX: R64.1, U1.B7 (UART0_RX/IR1_RX/PB23)
/UART0-TX: U1.A7 (UART0_TX/IR1_TX/PB22), UART0.1
/UBOOT_SEL: U1.W8 (UBOOT_SEL)
/UDM0: U1.N20 (DM0), USB_OTG224.D-
/UDM1: U1.P20 (DM1), USB_HOST1.2
/UDM2: U1.R20 (DM2), USB_HOST2.2
/UDP0: U1.N21 (DP0), USB_OTG224.D+
/UDP1: U1.P21 (DP1), USB_HOST1.3
/UDP2: U1.R21 (DP2), USB_HOST2.3
/USB0-IDDET: R55.2, U1.B5 (LCD1_D4/ATAD0/UART4_TX/EINT4/CSI1_D4/PH4), USB_OTG224.ID
/USB0-VBUSDET: C135.1, R51.1, R54.2, U1.C5 (LCD1_D5/ATAD1/UART4_RX/EINT5/CSI1_D5/PH5)
/USB1-DRV: R58.2, U1.A4 (LCD1_D6/ATAD2/UART5_TX/MS_BS/EINT6/CSI1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), U11.4 (EN)
/USB2-DRV: R62.2, U1.A5 (LCD1_D3/ATAIRQ/UART3_CTS/EINT3/CSI1_D3/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), U12.4 (EN)
/V+: 1.5V224.1, C1.1, C2.1, C3.2, C4.2, C5.2, C6.2, C7.2, C8.2, C9.2, C10.2, C11.2, C12.2, C19.2, C20.2, C21.2, C22.2, C23.2, C24.2, C25.2, C26.2, C27.2, C28.2, C29.2, C30.2, C31.2, C32.2, C33.2, C34.2, C35.2, C36.2, C47.2, C48.2, C49.2, C50.2, C51.2, C52.2, C53.2, C54.2, C55.2, C56.2, C57.2, C58.2, C59.2, C60.2, C61.2, C62.2, C63.2, C64.2, C201.1, C203.1, C204.1, L14.2, R1.2, R2.2, R6.2, R86.1, U1.G5 (VCC_DRAM), U1.H5 (VCC_DRAM), U1.L5 (VCC_DRAM), U1.M5 (VCC_DRAM), U1.R5 (VCC_DRAM), U1.T5 (VCC_DRAM), U1.W5 (VCC_DRAM), U1.W6 (VCC_DRAM), U1.W7 (VCC_DRAM), U1.Y6 (VCC_DRAM), U2.A1 (VDDQ), U2.A8 (VDDQ), U2.B2 (VDD), U2.C1 (VDDQ), U2.C9 (VDDQ), U2.D2 (VDDQ), U2.D9 (VDD), U2.E9 (VDDQ), U2.F1 (VDDQ), U2.G7 (VDD), U2.H2 (VDDQ), U2.H9 (VDDQ), U2.K2 (VDD), U2.K8 (VDD), U2.N1 (VDD), U2.N9 (VDD), U2.R1 (VDD), U2.R9 (VDD), U3.A1 (VDDQ), U3.A8 (VDDQ), U3.B2 (VDD), U3.C1 (VDDQ), U3.C9 (VDDQ), U3.D2 (VDDQ), U3.D9 (VDD), U3.E9 (VDDQ), U3.F1 (VDDQ), U3.G7 (VDD), U3.H2 (VDDQ), U3.H9 (VDDQ), U3.K2 (VDD), U3.K8 (VDD), U3.N1 (VDD), U3.N9 (VDD), U3.R1 (VDD), U3.R9 (VDD)
/VCC: 3.3V224.1, C74.2, C75.2, C76.2, C92.2, C93.2, C94.2, C95.2, C96.2, C97.2, C98.2, C99.2, C100.2, C113.2, C114.2, C120.2, C121.2, C130.2, C131.2, C132.2, C143.2, C144.2, C164.1, C165.2, C191.1, C194.1, C195.2, C196.1, C198.2, C211.1, C212.1, C213.1, L1.1, L2.1, L3.1, L5.1, L16.2, R20.1, R21.2, R22.1, R23.1, R24.2, R29.1, R30.2, R37.2, R39.1, R40.2, R41.2, R42.2, R55.1, R56.2, R57.2, R60.2, R61.2, R64.2, R79.2, R81.2, R91.1, R93.2, R94.2, R95.2, R96.2, RM1.1.2 (2), RM1.2.2 (2), RM1.3.2 (2), RM3.1.1 (1), RM3.2.1 (1), RM3.3.1 (1), RM3.4.1 (1), RM4.1.2 (2), RM4.2.2 (2), RM4.4.2 (2), U1.AB19 (HPVCCIN), U1.H8 (VCC), U1.H9 (VCC), U1.H10 (VCC), U1.H15 (VCC), U1.H19 (VCC_NAND), U1.J8 (VCC), U1.J9 (VCC), U1.J10 (VCC), U1.J14 (VCC), U1.J19 (VCC_NAND), U1.L15 (UVCC_T), U1.L16 (UVCC_C), U1.N19 (VCC_CARD), U1.P16 (PLLVP25), U1.T13 (VP_HDMI), U1.W12 (VCC_LVDS), U1.W13 (VCC_LVDS), U1.W14 (VCC_LVDS), U1.W15 (VCC33_TVOUT), U1.W16 (VCC33_TVIN), U4.12 (VCC), U4.37 (VCC), U6.8 (VCC), VR1.1 (VIN), VR1.3 (CE)
/VCC/2: 1.2V_CPU224.1, C65.2, C66.2, C67.2, C68.2, C69.2, C70.2, C166.1, C167.1, L12.2, U1.H11 (VDD_CPU), U1.H12 (VDD_CPU), U1.H13 (VDD_CPU), U1.H14 (VDD_CPU), U1.J12 (VDD_CPU), U1.J13 (VDD_CPU), U13.10 (DCDC2)
/VCCINT: 1.2V_INT224.1, C15.2, C16.2, C17.2, C18.2, C37.2, C38.2, C39.2, C40.2, C41.2, C42.2, C43.2, C44.2, C45.2, C46.2, C145.2, C148.2, C172.1, C173.1, C181.2, C184.2, L13.2, U1.J15 (VDD_INT), U1.J16 (VDD_INT), U1.K9 (VDD_INT), U1.K10 (VDD_INT), U1.K15 (VDD_INT), U1.K16 (ULVDD), U1.L8 (VDD_INT), U1.L9 (VDD_INT), U1.M8 (VDD_DLL), U1.M15 (VDD12_SATA), U1.M16 (VDD12_SATA), U1.N9 (VDD_DLL), U1.P9 (VDD_DLL), U1.R9 (VDD_INT), U1.R10 (VDD_INT), U1.T8 (VDD_INT), U13.17 (DCDC3)
/VDD: 2.5V224.1, C177.2, C178.2, C189.1, C190.2, C192.1, C193.1, U1.N15 (VDD25_SATA), U1.N16 (VDD25_SATA), U1.W17 (VDD25_TVIN), VR1.5 (VOUT)
/VDDREG1: C83.2, C84.2, C85.2, L3.2, U5.44 (VDDREG), U5.45 (VDDREG)
/VDD_RTC: C118.2, C119.2, C179.1, U1.K8 (RTC_VDD), U13.28 (LDO1)
/VGA-B: U1.AB16 (TVOUT1/VGA-B)
/VGA-G: U1.AC16 (TVOUT0/VGA-G)
/VGA-R: U1.AC17 (TVOUT2/VGA-R)
/VINT: C176.2, U13.26 (VINT)
/VMIC: U1.AA21 (VMIC)
/VPP: 3.0VA224.1, C123.2, C183.1, R87.1, U1.T19 (AVCC), U13.12 (LDO2), U15.1 (EN)
/WEN: U1.T3 (SWE), U2.L3 (#WE), U3.L3 (#WE)
/XTALI: C116.2, Q3.2, U1.N23 (CLK24M_IN)
/XTALO: C117.2, Q3.1, U1.N22 (CLK24M_OUT)
AVDD/DVDD(1.05V): L4.2
FMINL: GPIO-4.19
FMINR: GPIO-4.17
GND: FET2.2, GPIO-1.2, GPIO-2.2, GPIO-3.2, GPIO-4.2, LCD_CON224.2, LCD_CON224.4, PWR224.2_1, R83.1, RECOVERY224.1_1
GNDA: GPIO-1.4, R83.2
HPCOM: GPIO-1.16
HPOUTL: GPIO-1.14
HPOUTR: GPIO-1.18
IPSOUT: RESET224.1_1
LCD_CLK: LCD_CON224.31
LCD_D0: LCD_CON224.21
LCD_D1: LCD_CON224.22
LCD_D2: LCD_CON224.23
LCD_D3: LCD_CON224.24
LCD_D4: LCD_CON224.25
LCD_D5: LCD_CON224.26
LCD_D6: LCD_CON224.27
LCD_D7: LCD_CON224.28
LCD_D8: LCD_CON224.13
LCD_D9: LCD_CON224.14
LCD_D10: LCD_CON224.15
LCD_D11: LCD_CON224.16
LCD_D12: LCD_CON224.17
LCD_D13: LCD_CON224.18
LCD_D14: LCD_CON224.19
LCD_D15: LCD_CON224.20
LCD_D16: LCD_CON224.5
LCD_D17: LCD_CON224.6
LCD_D18: LCD_CON224.7
LCD_D19: LCD_CON224.8
LCD_D20: LCD_CON224.9
LCD_D21: LCD_CON224.10
LCD_D22: LCD_CON224.11
LCD_D23: LCD_CON224.12
LCD_DE: LCD_CON224.32
LCD_HSYNC: LCD_CON224.29
LCD_PWR: LCD_CON224.35
LCD_VSYNC: LCD_CON224.30
LDO3_2.8V: GPIO-2.4
LINEINL: GPIO-4.15
LINEINR: GPIO-4.13
LRADC0: GPIO-1.6
LRADC1: GPIO-1.8
MIC1OUTN: GPIO-4.8
MIC1OUTP: GPIO-4.6
MICIN1: GPIO-1.10
MICIN2: GPIO-4.10
NMI_N: GPIO-4.4
unnamed: U13.N1 (GND_PAD), U13.N2 (GND_PAD), U13.N3 (GND_PAD), U13.N4 (GND_PAD), U13.N5 (GND_PAD), U13.N6 (GND_PAD), U13.N7 (GND_PAD), U13.N8 (GND_PAD), U13.N9 (GND_PAD), U13.N10 (GND_PAD), U13.N11 (GND_PAD), U13.N12 (GND_PAD), U13.N13 (GND_PAD), U13.N14 (GND_PAD), U13.N15 (GND_PAD), U13.N16 (GND_PAD), U13.N17 (GND_PAD)
PA9: GPIO-4.12
PA14: GPIO-4.14
PB2/PWM0: LCD_CON224.36
PB3: GPIO-3.4
PB4: GPIO-3.6
PB5: GPIO-3.8
PB6: GPIO-3.10
PB7: GPIO-3.12
PB8/SATA-PWR-EN: GPIO-3.14
PB9: GPIO-3.16
PB10: GPIO-3.18
PB11: GPIO-3.20
PB12: GPIO-3.22
PB13: GPIO-3.24
PB14: GPIO-3.26
PB15: GPIO-3.28
PB16: GPIO-3.30
PB17: GPIO-3.32
PB18: GPIO-1.36
PB19: GPIO-1.34
PB20: GPIO-1.32
PB21: GPIO-1.30
PC3/SATA-PWR-EN: GPIO-1.29
PC7: GPIO-4.16
PC16/NWP: GPIO-4.18
PC17/USB0-DRV: GPIO-4.20
PC18: GPIO-1.31
PC19: GPIO-1.33
PC20: GPIO-1.35
PC21: GPIO-1.37
PC22: GPIO-1.39
PC23: GPIO-1.40
PC24: GPIO-1.38
PE0: GPIO-2.6
PE1: GPIO-2.8
PE2: GPIO-2.10
PE3: GPIO-2.12
PE4: GPIO-2.14
PE5: GPIO-2.16
PE6: GPIO-2.18
PE7: GPIO-2.20
PE8: GPIO-2.22
PE9: GPIO-2.24
PE10: GPIO-2.26
PE11: GPIO-2.28
PG0: GPIO-1.5
PG1: GPIO-1.7
PG2: GPIO-1.9
PG3: GPIO-1.11
PG4: GPIO-1.13
PG5: GPIO-1.15
PG6: GPIO-1.17
PG7: GPIO-1.19
PG8: GPIO-1.21
PG9: GPIO-1.23
PG10: GPIO-1.25
PG11: GPIO-1.27
PH0: GPIO-3.7
PH7: GPIO-3.9
PH9: GPIO-3.11
PH10: GPIO-3.13
PH11: GPIO-3.15
PH12: GPIO-3.17
PH13: GPIO-3.19
PH14: GPIO-3.21
PH15: GPIO-3.23
PH16: GPIO-3.25
PH17: GPIO-3.27
PH18: GPIO-3.29
PH19: GPIO-3.31
PH20: GPIO-3.33
PH21: GPIO-3.35
PH22: GPIO-3.37
PH23: GPIO-3.39
PH24: GPIO-3.34
PH25: GPIO-3.36
PH26: GPIO-3.38
PH27: GPIO-3.40
PI0: GPIO-2.9
PI1: GPIO-2.11
PI2: GPIO-2.13
PI3: GPIO-2.15
PI4: GPIO-2.17
PI5: GPIO-2.19
PI6: GPIO-2.21
PI7: GPIO-2.23
PI8: GPIO-2.25
PI9: GPIO-2.27
PI10: GPIO-2.29
PI11: GPIO-2.31
PI12: GPIO-2.33
PI13: GPIO-2.35
PI14: GPIO-2.37
PI15: GPIO-2.39
PI16: GPIO-2.40
PI17: GPIO-2.38
PI18: GPIO-2.36
PI19: GPIO-2.34
PI20: GPIO-2.32
PI21: GPIO-2.30
RESET_N: GPIO-3.5
TPX1: LCD_CON224.37
TPX2: LCD_CON224.38
TPY1: LCD_CON224.39
TPY2: LCD_CON224.40
TVIN0: GPIO-4.5
TVIN1: GPIO-4.7
TVIN2: GPIO-4.9
TVIN3: GPIO-4.11
TVOUT3: GPIO-4.3
TWI0-SCK: GPIO-2.5
TWI0-SDA: GPIO-2.7
UART0-RX: D2.A, GPIO-1.26
UART0-TX: GPIO-1.28
UBOOT_SEL: RECOVERY224.2_1
VCC: D1.A, GPIO-1.3, GPIO-2.3, GPIO-3.3, GPIO-4.1, LCD_CON224.3
VGA-B: GPIO-1.22
VGA-G: GPIO-1.20
VGA-R: GPIO-1.24
VMIC: GPIO-1.12

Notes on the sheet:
POWER SUPPLY CIRCUIT
LI-ION_BATTERY
1 x [4Gb DDR3 SDRAM (256Mx16)]
MicroSD
5VDC Only!!!
BUTTON
USB-OTG
Iset = 6800/Rs
Iset = 523mA
USB-HOSTs
1V3/30mA
3V/200mA
2V8/200mA
1V2/1.2A
1V2/1.6A
HSYNC
VSYNC
3.3V
GND
5.0V
CLK
PWRE
BKL
L/R
U/D
NAND Flash
32Gb (4096M x 8bit)
GPIO EXTENSION
LCD EXTENSION
Must be Floating!!!
EEPROM
MAC Address
16 Kbit
(2048 x 8)
HDMI
Iset = 1000mA
SATA
LED
Vout=0.6x(1+Rc/Rd)
Vout=0.6x(1+Re/Rf)

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
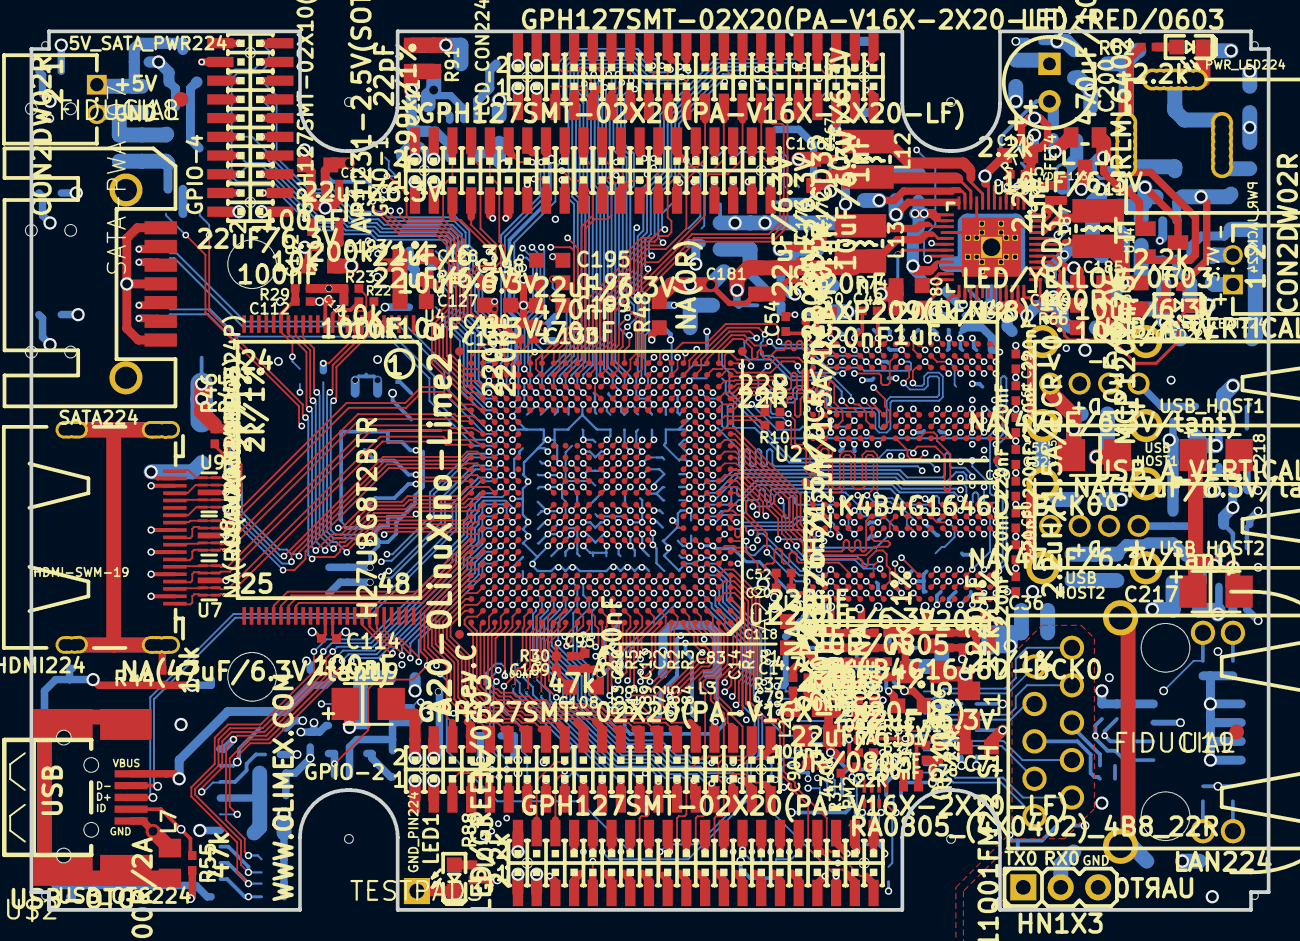
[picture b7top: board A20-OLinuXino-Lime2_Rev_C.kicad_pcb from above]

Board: 8 copper layers, 84.0 x 59.6 mm, 420 parts (0 on the bottom side), 290 nets.

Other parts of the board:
U$2: HAMMOND_1593LBK_A10_LIME
U$5: LOGO-OPENHARDWARE_8X8
U$6: OLIMEX1_V
U$9: PB
U$10: ESD_SYMBOL
U$11: RECYCLE_BIN1%2f8
U$12: ROHS
